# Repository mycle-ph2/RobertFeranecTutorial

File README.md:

# RobertFeranacTutorial

## Summary
My first schematic and Printed Circuit Board (Assembly) 
Designed in KiCad.
This schematic was based on the tutorial by Robert Feranec: [video link](https://www.youtube.com/watch?v=maaBkw7IRUc)

## The Purpose of This Assembly 
* This assembly connects an LED which can be connected to for example an Arduino UNO.
* This assembly introduces concepts like layers and component connections in PCB Design.
* This project gives practice in saving files, including information about the schematic, BOM, footprint positions, and more.

## 3D Model

## Schematic

## Components List
* Resistor
* Diode
* J1 Connector
* 3.3V Power Source

## Things I learned
* Create a custom symbol for a component
* Find existing components from a library
* Attach a Footprint to a Component Symbol
* Work with different layers in the PCB Design, including Cu, Edge, FAB, Silkscreen, and more.
* View a 3D Model
* Run DRC Check and resolve errors

## An edit from a Fork at Forrest Erickson
This Project was created in June of 2025

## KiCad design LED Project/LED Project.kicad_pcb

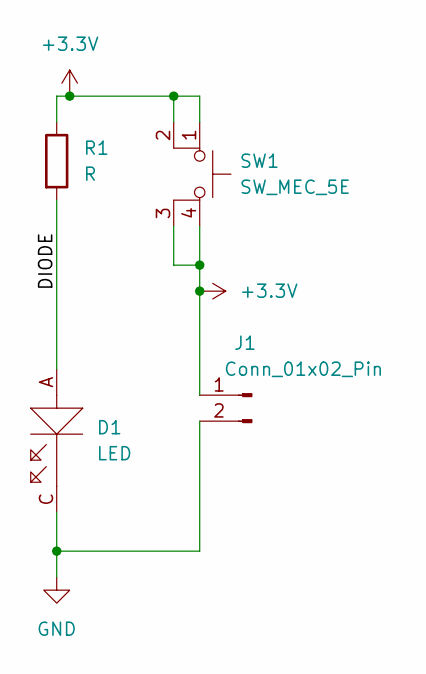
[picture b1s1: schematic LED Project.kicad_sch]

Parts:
D1: LED; LED0603
J1: Conn_01x02_Pin; Molex_KK-254_AE-6410-02A_1x02_P2.54mm_Vertical
R1: R; R_0805_2012Metric
SW1: SW_MEC_5E; SW_SPST_SKQG_WithStem

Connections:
+3.3V: J1.1, R1.1, SW1.1, SW1.2, SW1.3 (K), SW1.4 (A)
/DIODE: D1.A (Anode), R1.2
GND: D1.C (Cathode), J1.2

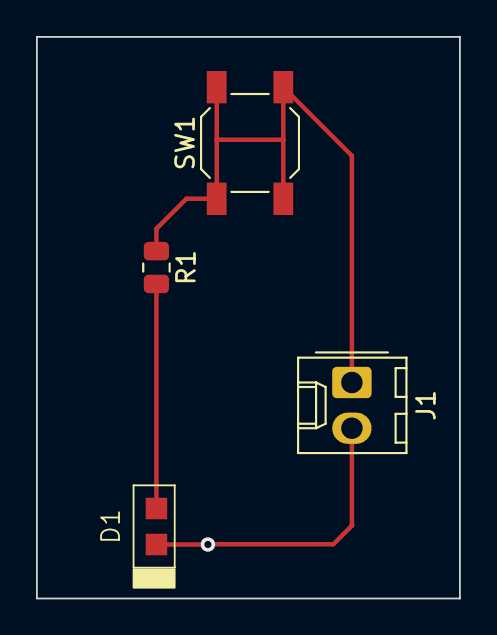
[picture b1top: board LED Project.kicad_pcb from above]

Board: 2 copper layers, 23.5 x 31.2 mm, 4 parts (0 on the bottom side), 3 nets.

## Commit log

2025-06-24 Initial Tutorial
2025-07-02 Update README.md
    Lee's demonstration of some markdown features.
2025-07-02 Update README.md
    Change in Lee's Fork to the main readme mark down.
2025-07-06 Try to add link
2025-07-08 ON-OFF-LAMP First Trial
2025-07-08 update backup
2025-07-08 Images
